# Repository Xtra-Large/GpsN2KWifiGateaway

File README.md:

# GpsN2KWifiGateaway

Ce projet est encore en développement, n'hésitez pas à participer!

## Présentation

L'objectif initial de ce projet etait de disposer d'un GPS NMEA 2000 ayant une fréquence de rafraichissement d'au moins 10Hz pour l'intégrer dans notre Archambault A31 (https://epsilon3dsailingteam.fr/).

Il semble que les pilotes automatiques intègrent les données GPS pour effectuer des corrections de trajectoire.

Les GPS Ublox M8N (assez peu couteux) permettent, apèrs configuration, d'obtenir ces taux de rafraichissement en étant mono constellation.
Le nouveelles puces M9N permettent d'obtenir un taux de rafraichissement de 25Hz en exploitant les 4 constellations (GPS, Glonass, Galiléo et Baidoo).

## Projet

Le projet est constitué : 
- Une partie électronique constituée :
  - D'une puce ESP 32 
  - D'un puce GPS M9N, dans la première version nous utilisons une carte Sparkfun (https://www.sparkfun.com/products/15712)
- Un boitier à imprimer en 3D (en cours)
- Le code source du projet

Le code source peut être ouvert avec l'IDE Arduino et le projet électronique avec kiCAD

## Librairies externes utilisées

Le code source utilise ces librairies, sous licence MIT elles aussi :
- Plusieurs librairies de, https://github.com/ttlappalainen : NMEA0183, NMEA2000, NMEA2000_esp32
- https://github.com/ronzeiller/NMEA0183-AIS
- https://github.com/sparkfun/SparkFun_u-blox_GNSS_Arduino_Library

## Fonctions implémentées

Actuellement le projet permet :
- D'injecter sur le réseau NMEA2000 les données de la puce GPS a la fréquence de 20Hz (25Hz possible, a voir l'intérêt)
- Se connecter à un réseau Wifi existant
- Creer un point d'accès Wifi
- Lire les données du réseau NMEA2000, les convertir en MNEA0183 et les router vers :
-- 3 ports série 
-- Wifi en TCP et en UDP

## RoadMap
- Page Web de configuration visualisation
  - Ajout du serveur de configuration Wifi pour configuration sur un routeur externe
  - Ajout de fonction AJAX/JSON pour rechargement de la page de statut
  - Mise en une seule page pour intégrer la fonction de MAJ du firmware
  - Ajout d'option pour activer certaines redirections vers les ports et le reseau (a stocker en NVS)
  - Mise en page et logo
  - Configuration des ports de sortie serie : Msg NMEA, vitesse, activation...
  - Configuration du SSID externe + PWD

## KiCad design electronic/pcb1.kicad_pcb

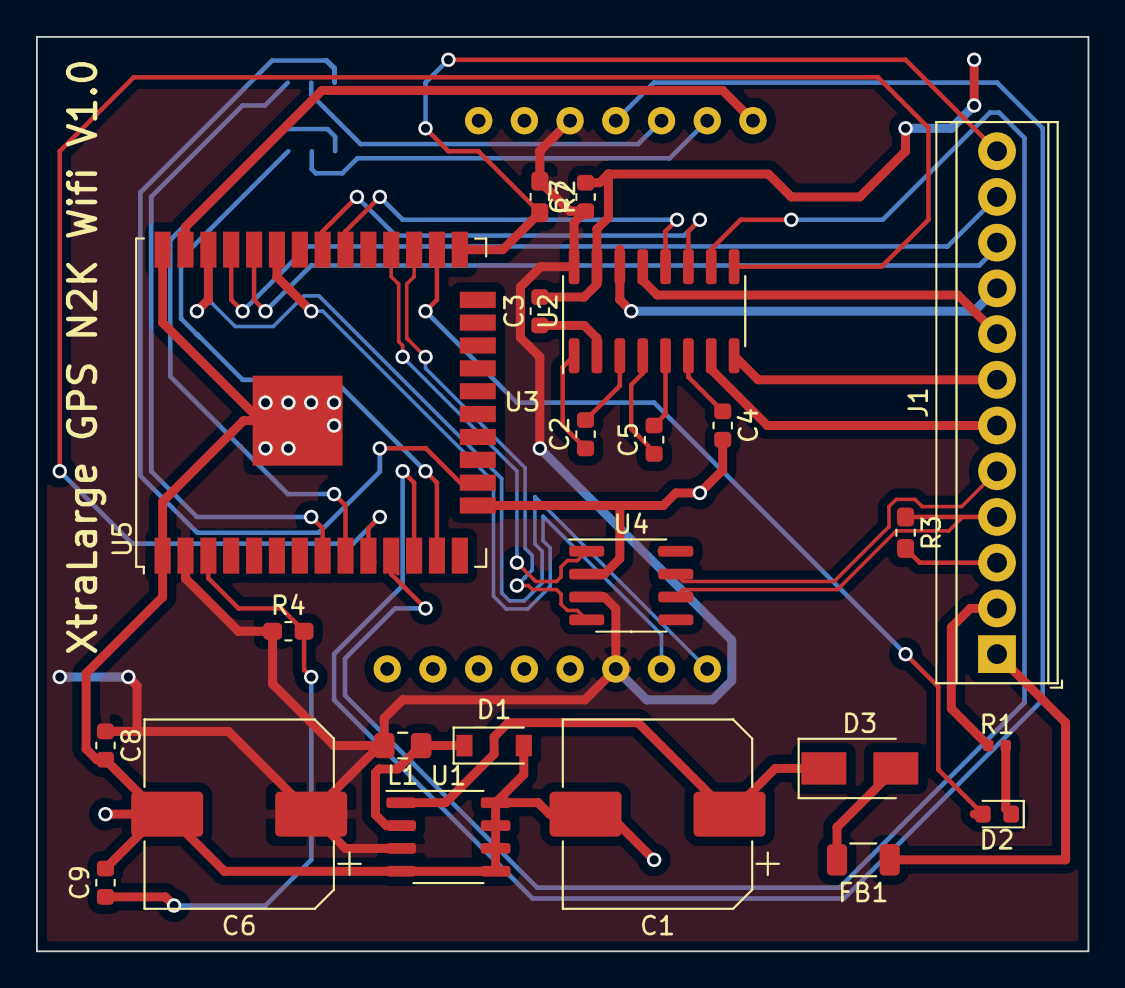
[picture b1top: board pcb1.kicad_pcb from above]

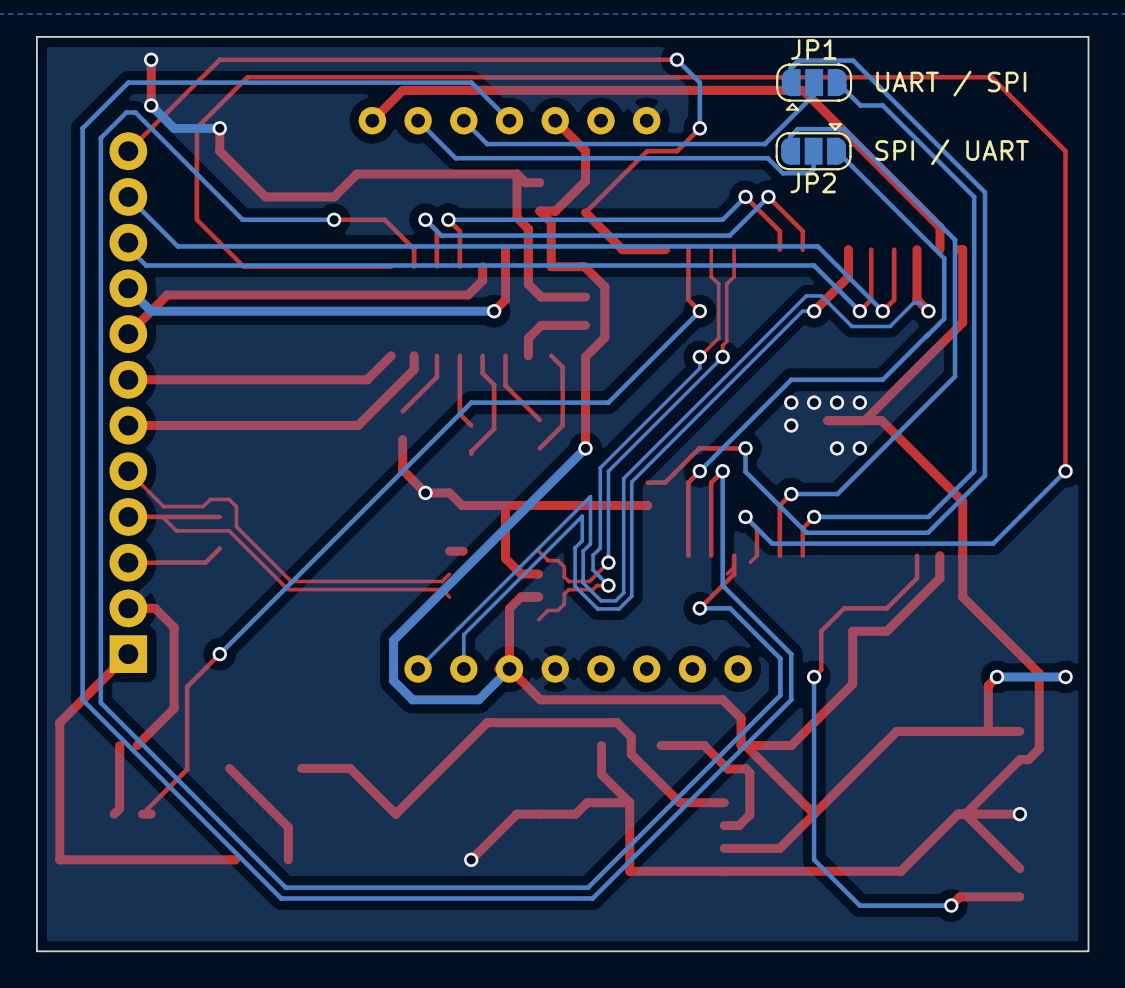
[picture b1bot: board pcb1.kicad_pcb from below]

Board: 2 copper layers, 58.4 x 50.8 mm, 26 parts (2 on the bottom side), 41 nets.

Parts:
C1: 470UF; CP_Elec_10x10
C2, C3, C4, C5, C7: 0.1uF; C_0603_1608Metric
C6: 330uF; CP_Elec_10x10
C8: 10uF; C_0603_1608Metric
C9: 2.2uF; C_0603_1608Metric
D1: D_1N5819; D_SOD-123
D2: Green; LED_0603_1608Metric
D3: D_Schottky; D_SMA
FB1: 100MHz 6A; R_1206_3216Metric
J1: Conn_01x12; TerminalBlock_TE_1-282834-2_1x12_P2.54mm_Horizontal
JP1: MOSI/RX; SolderJumper-3_P1.3mm_Open_RoundedPad1.0x1.5mm
JP2: MISO/TX; SolderJumper-3_P1.3mm_Open_RoundedPad1.0x1.5mm
L1: 47uH; L_0805_2012Metric_Pad1.15x1.40mm_HandSolder
R1: 220ohm; R_0402_1005Metric
R2, R4: 10kohm; R_0603_1608Metric_Pad1.05x0.95mm_HandSolder
R3: 120ohm; R_0603_1608Metric_Pad1.05x0.95mm_HandSolder
U1: XLSEMI XL1509-3.3E1; SOP-8_3.9x4.9mm_P1.27mm
U2: MAX3232CDR; SOIC-16_3.9x9.9mm_P1.27mm
U3: SparkfunM9N; AdafruitGPSM9N
U4: SN65HVD232DR; SOIC-8_3.9x4.9mm_P1.27mm
U5: ESP32-WROOM-32U

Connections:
+3V3: C6.1, C7.1, C8.1, L1.2, R2.1, R4.1, U1.3, U2.16, U3.6, U3.11, U4.3, U5.2
+BATT: FB1.1, J1.1
/CANX_N: U4.4, U5.27
/CANX_P: U4.1, U5.28
/CAN_N: J1.4, R3.1, U4.6
/CAN_P: J1.5, U4.7
/EN: C9.1, R4.2, U5.3
/ESP_LED_CTRL: D2.2, U5.26
/GPIO0: J1.12, R2.2, U5.25
/I2C_N: U3.7, U5.33
/I2C_P: U3.8, U5.36
/RS232_TX1: J1.9, U2.14
/RX232_RX1: J1.8, U2.13
/RX232_RX2: J1.7, U2.8
/RX232_TX2: J1.6, U2.7
/RX_FLASH: J1.10, U5.34
/RX_UART1: U2.12, U5.30
/RX_UART2: U2.9, U5.10
/TX_FLASH: J1.11, U5.35
/TX_UART1: U2.11, U5.31
/TX_UART2: U2.10, U5.11
GND: C1.2, C3.2, C4.2, C6.2, C7.2, C8.2, C9.2, D1.2, J1.2, R1.1, U1.4, U1.5, U1.6, U1.7, U1.8, U2.15, U3.5, U3.9, U4.2, U5.1, U5.15, U5.38, U5.39
GPS_RX: JP1.1, U5.16
GPS_TX: JP2.1, U5.13
unnamed: C1.1, D3.1, U1.1
unnamed: C2.1, U2.1
unnamed: C2.2, U2.3
unnamed: C3.1, U2.2
unnamed: C4.1, U2.6
unnamed: C5.1, U2.4
unnamed: C5.2, U2.5
unnamed: D1.1, L1.1, U1.2
unnamed: D2.1, R1.2
unnamed: D3.2, FB1.2
unnamed: J1.3, R3.2
unnamed: JP1.2, U3.13
unnamed: JP2.2, U3.14
SPI_CS: U3.12, U5.12
SPI_MISO: JP2.3, U5.9
SPI_MOSI: JP1.3, U5.8
SPI_SCK: U3.15, U5.37

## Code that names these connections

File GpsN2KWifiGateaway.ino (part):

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//#define ESP32_CAN_RX_PIN GPIO_NUM_4
#define ESP32_CAN_TX_PIN GPIO_NUM_17
#define ESP32_CAN_RX_PIN GPIO_NUM_16
#define SPI_SCK GPIO_NUM_23
#define SPI_CS GPIO_NUM_27
#define SPI_MOSI GPIO_NUM_32
#define SPI_MISO GPIO_NUM_33

//#include <HardwareSerial.h>
//HardwareSerial MySerial1(1);
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
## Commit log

2021-04-08 Creation
2021-04-08 1ere version partie en prodcution
    Modification sur les pin de l'ESP32 utilisés,
    Modification de quelques composants
    ajout de toutes les références
2021-04-08 Ajout de la vue 3D
2021-04-13 Version 1.0 proto commande JLCPCB
2021-04-13 Intégration du dome du couvercle dans le couvercle
2024-11-25 Update BoardSerialNumber.cpp
    MAJ des librairies
2024-11-25 Update GpsN2KWifiGateaway.ino
    MAJ des librairies
2024-11-25 Update N2kDataToNMEA0183.cpp
    MAJ des librairies
2024-11-25 Update GpsN2KWifiGateaway.ino
    Ajout d'un commentaire sur la librairie Blink Control

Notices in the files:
GpsN2KWifiGateaway.ino:
Copyright (c) 2021-2025 Aurelien TRICAULT - XtraLarge
Copyright Dronotique - Aurélien TRICAULT
